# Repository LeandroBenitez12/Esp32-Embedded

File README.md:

# Esp32-Embedded
# Esp32-Embedded

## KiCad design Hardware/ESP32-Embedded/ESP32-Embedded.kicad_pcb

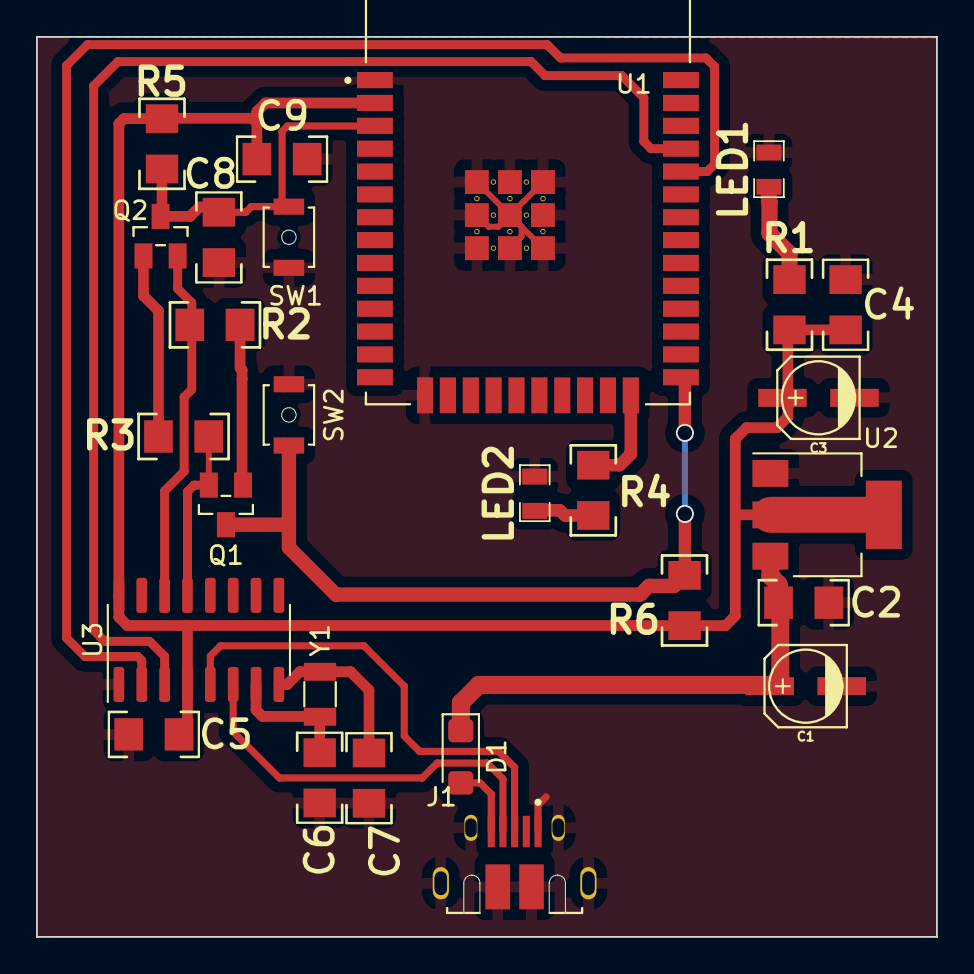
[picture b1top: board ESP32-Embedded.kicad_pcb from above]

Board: 2 copper layers, 50.0 x 50.0 mm, 27 parts (0 on the bottom side), 19 nets.

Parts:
C1, C3: 10uF; CAP_ELEC_SMD_4X5.5
C2, C4, C5, C8, C9: 100nF; C_1206
C6, C7: 22pF; C_1206
D1: 5V; D_SMF
J1: Micro USB; AMPHENOL_10103592-0001LF
LED1, LED2: 2V; R_0805
Q1, Q2: S8050; SOT-23_BEC
R1, R4: 220; R_1206
R2, R3, R5, R6: 10K; R_1206
SW1: EN; SW_SPST_B3U-1000P-B
SW2: BOOT; SW_SPST_B3U-1000P-B
U1: ESP32-WROOM-32E; MODULE_ESP32-WROOM-32D
U2: AMS1117-3.3; SOT-223-3_TabPin2
U3: CH340G; SOIC-16_3.9x9.9mm_P1.27mm
Y1: 12Mhz; Crystal_SMD_3215-2Pin_3.2x1.5mm

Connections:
+3V3: C3.1, C4.1, C5.1, C9.2, R1.1, R5.2, R6.2, U1.2 (3V3), U2.2 (VO), U3.4 (V3), U3.16 (VCC)
+5V: C1.1, C2.1, D1.1 (K), U2.3 (VI)
/D+: J1.3 (D+), U3.5 (UD+)
/D-: J1.2 (D-), U3.6 (UD-)
/DTR: Q1.E, R3.1, U3.13 (~DTR)
/EN: C8.1, Q2.C, R5.1, SW1.2, U1.3 (EN)
/IO0: Q1.C, R6.1, SW2.2, U1.25 (IO0)
/IO2: R4.1, U1.24 (IO2)
/RTS: Q2.E, R2.1, U3.14 (~RTS)
/RXD0: U1.34 (RXD0), U3.2 (TXD)
/TXD0: U1.35 (TXD0), U3.3 (RXD)
GND: C1.2, C2.2, C3.2, C4.2, C5.2, C6.2, C7.2, C8.2, C9.1, J1.5 (GND), J1.S1 (SHIELD), J1.S3 (SHIELD), J1.S4 (SHIELD), J1.S5 (SHIELD), J1.S6 (SHIELD), LED1.2 (K), LED2.2 (K), SW1.1, SW2.1, U1.1 (GND), U1.15 (GND), U2.1 (GND), U3.1 (GND)
unnamed: D1.2 (A), J1.1 (VDD)
unnamed: LED1.1 (A), R1.2
unnamed: LED2.1 (A), R4.2
unnamed: Q1.B, R2.2
unnamed: Q2.B, R3.2
unnamed: C6.1, U3.7 (XI), Y1.1
unnamed: C7.1, U3.8 (XO), Y1.2

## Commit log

2023-06-06 iniciando poryecto
2023-06-06 sch en proceso faltan cositas
2023-06-06 sch casi terminado ordene y agregue pocas cosas
2023-06-07 sch terminado
2023-06-07 agregue foots ,inicie pcb ordene componentes
2023-06-08 ordenando componentes en placa
2023-06-09 placa con esp32 embebido y 5 puentes lista
2023-06-09 placa v2 con 3 puentes
2023-06-09 Hice cambios de tamaño de pistas y margen de gnd añadi 3d a componentes y agregue imagenes de los 3D
2023-06-13 Cambios importantes correcciones con Bustos placa lista
2023-06-13 Cambios de encapsulados
2023-08-22 realice modificaciones importantes en sch para guia de eze y nueva placa para pcbway
